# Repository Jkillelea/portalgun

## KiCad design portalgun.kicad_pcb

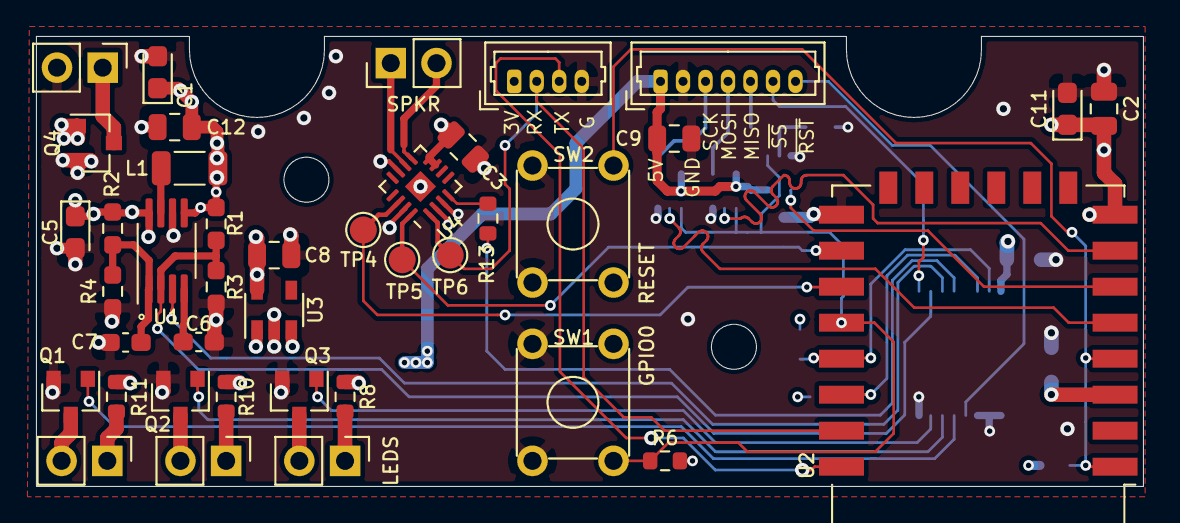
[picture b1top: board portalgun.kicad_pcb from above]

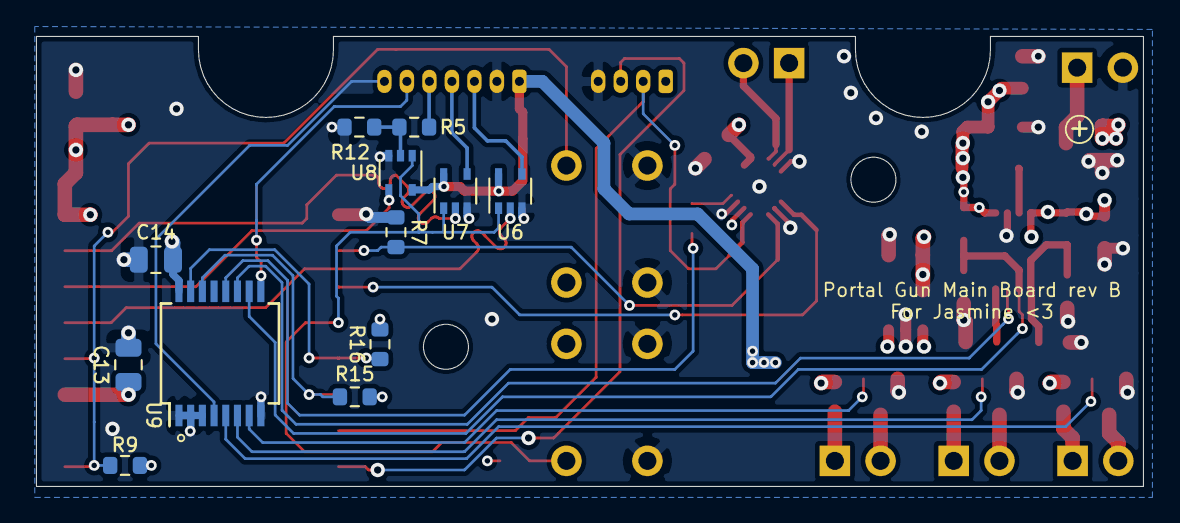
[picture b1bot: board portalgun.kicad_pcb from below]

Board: 4 copper layers, 61.5 x 25.0 mm, 54 parts (12 on the bottom side), 40 nets.

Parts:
C1, C5, C11: 10uF; CP_EIA-2012-15_AVX-P
C2, C3, C8, C9, C12, C13, C14: 1uF; C_0805_2012Metric
C6: 200nF; C_0603_1608Metric_Pad1.08x0.95mm_HandSolder
C7: 10pF; C_0603_1608Metric_Pad1.08x0.95mm_HandSolder
H1, H2: MountingHole; MountingHole_2.5mm
J1, J3, J4, J5, J10: Conn_01x02_Male; PinHeader_1x02_P2.54mm_Vertical
J2: Conn_01x07_Male; Molex_PicoBlade_53047-0710_1x07_P1.25mm_Vertical
J9: Conn_01x04_Female; Molex_PicoBlade_53047-0410_1x04_P1.25mm_Vertical
L1: 10uH; L_1206_3216Metric
Q1, Q2, Q3: BS316N; SOT-23
Q4: Q_PMOS_DGS; SOT-23
R1: 56k; R_0603_1608Metric_Pad0.98x0.95mm_HandSolder
R2: 383k; R_0603_1608Metric_Pad0.98x0.95mm_HandSolder
R3: 47k; R_0603_1608Metric_Pad0.98x0.95mm_HandSolder
R4: 120k; R_0603_1608Metric_Pad0.98x0.95mm_HandSolder
R5: 1k; R_0603_1608Metric
R6, R7, R9, R12, R15, R16: 10k; R_0603_1608Metric
R8, R10, R11: 200; R_0603_1608Metric
R13: 634kR; R_0603_1608Metric
SW1, SW2: SW_MEC_5E; SW_TH_Tactile_Omron_B3F-10xx
TP4: I2S_LRCIN_TP; TestPoint_Pad_D1.5mm
TP5: I2S_BCLK_TP; TestPoint_Pad_D1.5mm
TP6: I2S_DIN_TP; TestPoint_Pad_D1.5mm
U1: NCP1421; MSOP-8_3x3mm_P0.65mm
U2: ESP-12F; ESP-12E
U3: MIC5504-3.3YM5; SOT-23-5
U4: MAX98357AETE; TQFN-16-1EP_3x3mm_P0.5mm_EP1.23x1.23mm
U6, U7, U8: 74AHC1G125; SOT-353_SC-70-5
U9: PCA9534; SSOP-16_5.3x6.2mm_P0.65mm

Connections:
+3V3: C2.1, C3.1, C8.1, C11.1, C13.1, C14.1, J9.1, R6.2, R9.1, R15.1, R16.2, U2.3, U2.8, U3.5, U4.2, U4.7, U4.8, U9.16
+5V: C5.1, C9.1, J2.1, R2.1, R8.2, R10.2, R11.2, U1.8, U3.1, U3.3, U6.5, U7.5, U8.5
/Audio DAC/AOUT+: J4.1, U4.10
/Audio DAC/AOUT-: J4.2, U4.9
/Audio DAC/~SD_MODE: R13.1, U4.4
/Audio DAC/~SHUTDOWN: R13.2, U9.12
/EXT_MISO: J2.5, R5.1
/EXT_MOSI: J2.4, U7.4
/EXT_SCK: J2.3, U6.4
/bat+: J1.1, Q4.3
/ncp_fb: C7.1, R2.2, R4.1, U1.1
/ncp_lx: L1.2, U1.7
/ncp_ref: C6.1, U1.4
/~rst: R9.2, SW2.4, U2.1, U2.4
ESP_RXD: J9.2, TP6.1, U2.21, U4.1
ESP_TXD: J9.3, U2.22
GND: C1.2, C2.2, C3.2, C5.2, C6.2, C7.2, C8.2, C9.2, C11.2, C12.2, C13.2, C14.2, J1.2, J2.2, J9.4, Q1.2, Q2.2, Q3.2, Q4.2, R3.2, R4.2, R7.1, R12.1, SW1.1, SW1.2, SW2.1, SW2.2, U1.6, U2.15, U3.2, U4.3, U4.11, U4.15, U4.17, U6.3, U7.3, U8.3, U9.1, U9.2, U9.3, U9.8
I2S_BCLK: R7.2, TP5.1, U2.16, U4.16
I2S_LRCLK: TP4.1, U2.17, U4.14
LED1: Q1.1, U9.5
LED2: Q2.1, U9.6
LED3: Q3.1, U9.7
NCP_LBI_EN: R1.2, R3.1, U1.2, U9.10
NCP_LBO: U1.3, U9.11
unnamed: J3.1, R8.1
unnamed: J3.2, Q3.3
unnamed: J5.1, R10.1
unnamed: J5.2, Q2.3
unnamed: J10.1, R11.1
unnamed: J10.2, Q1.3
unnamed: R5.2, R12.2, U8.2
SCL: R15.2, U2.20, U9.14
SDA: R16.1, U2.19, U9.15
SPI1_MISO: U2.6, U8.4
SPI1_MOSI: U2.7, U7.2
SPI1_SCK: U2.5, U6.2
VBAT: C1.1, C12.1, L1.1, Q4.1, R1.1, U1.5
~BUFFER_EN: R6.1, SW1.3, U2.18, U6.1, U7.1, U8.1
~DISPLAY_RST: J2.7, U9.4
~SPI1_SS: J2.6, U9.9

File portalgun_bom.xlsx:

Refs | Val | Footprint | Qty | Stock
> J1, J3-J5, J10 | Conn_01x02_Male | Connector_PinHeader_2.00mm:PinHeader_1x02_P2.00mm_Vertical | 5 | 5
J2 | Conn_01x07_Male | Connector_Molex:Molex_PicoBlade_53047-0710_1x07_P1.25mm_Vertical | 1 | 10
J9 | Conn_01x04_Female | Connector_Molex:Molex_PicoBlade_53047-0410_1x04_P1.25mm_Vertical | 1 | 10
> Q1-Q3 | BS316N | Package_TO_SOT_SMD:SOT-23 | 3 | 100
R1 | 56k | Resistor_SMD:R_0603_1608Metric_Pad0.98x0.95mm_HandSolder | 1 | 100
R2 | 383k | Resistor_SMD:R_0603_1608Metric_Pad0.98x0.95mm_HandSolder | 1 | 100
R3 | 47k | Resistor_SMD:R_0603_1608Metric_Pad0.98x0.95mm_HandSolder | 1 | 100
R4 | 120k | Resistor_SMD:R_0603_1608Metric_Pad0.98x0.95mm_HandSolder | 1 | 100
R5 | 1k | Resistor_SMD:R_0603_1608Metric | 1 | 100
> R8, R10, R11 | 200 | Resistor_SMD:R_0603_1608Metric | 3 | 100
> R6, R9, R15, R16 | 10k | Resistor_SMD:R_0603_1608Metric | 4 | 100
> SW1, SW2 | SW_MEC_5E | Button_Switch_THT:SW_TH_Tactile_Omron_B3F-10xx | 2 | 25
U3 | MIC5504-3.3YM5 | Package_TO_SOT_SMD:SOT-23-5 | 1 | 25
U5 | MIC5504-1.8YM5 | Package_TO_SOT_SMD:SOT-23-5 | 1 | 10
> U6-U8 | 74AHC1G125 | Package_TO_SOT_SMD:SOT-353_SC-70-5 | 3 | 25
U1 | NCP1421 | Package_SO:MSOP-8_3x3mm_P0.65mm | 1 | 4
> H1, H2 | MountingHole | MountingHole:MountingHole_2.5mm | 2 | 2
U4 | SGTL5000XNLA3 | Package_DFN_QFN:QFN-20-1EP_3x3mm_P0.4mm_EP1.65x1.65mm | 1 | 3
L1 | 10uH | Inductor_SMD:L_1206_3216Metric | 1 | 5
U2 | ESP-12F | RF_Module:ESP-12E | 1 | 5
> C1, C5, C11 | 10uF | Capacitor_Tantalum_SMD:CP_EIA-2012-15_AVX-P | 3 | 8
C4 | 100nF | Capacitor_SMD:C_0603_1608Metric | 1 | 10
C6 | 200nF | Capacitor_SMD:C_0603_1608Metric_Pad1.08x0.95mm_HandSolder | 1 | 10
C7 | 10pF | Capacitor_SMD:C_0603_1608Metric_Pad1.08x0.95mm_HandSolder | 1 | 10
> C3, C8-C10 | 1uF | Capacitor_SMD:C_0603_1608Metric | 4 | 10
C2 | 10uF | Capacitor_SMD:C_0805_2012Metric | 1 | 80

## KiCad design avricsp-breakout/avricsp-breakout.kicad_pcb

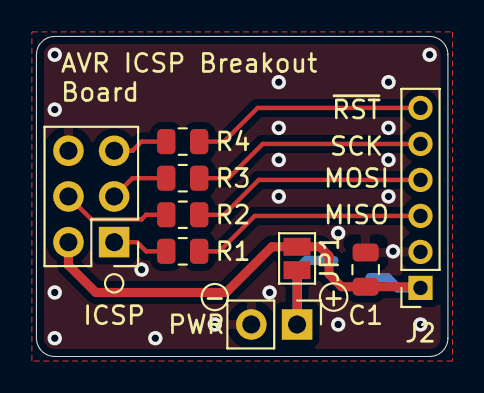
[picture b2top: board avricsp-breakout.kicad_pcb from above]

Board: 2 copper layers, 22.9 x 17.8 mm, 10 parts (1 on the bottom side), 11 nets.

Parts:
C1: 1uf; C_0805_2012Metric
ICSP: AVR-ISP-6; PinHeader_2x03_P2.54mm_Vertical
J2: Conn_01x06; PinSocket_1x06_P2.00mm_Vertical
JP1: SolderJumper_2_Open; SolderJumper-2_P1.3mm_Open_Pad1.0x1.5mm
PWR: Conn_01x02; PinHeader_1x02_P2.54mm_Vertical
Q1: Si2333CDS; SOT-23
R1, R2, R3, R4: 1k; R_0805_2012Metric

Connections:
/MISO: J2.3, R1.1
/MOSI: J2.4, R2.1
/SCK: J2.5, R3.1
/Vraw+: JP1.2, PWR.1, Q1.3
/~RST: J2.6, R4.1
GND: C1.2, ICSP.6, J2.2, PWR.2, Q1.1
unnamed: ICSP.1, R1.2
unnamed: ICSP.3, R3.2
unnamed: ICSP.4, R2.2
unnamed: ICSP.5, R4.2
VCC: C1.1, ICSP.2, J2.1, JP1.1, Q1.2

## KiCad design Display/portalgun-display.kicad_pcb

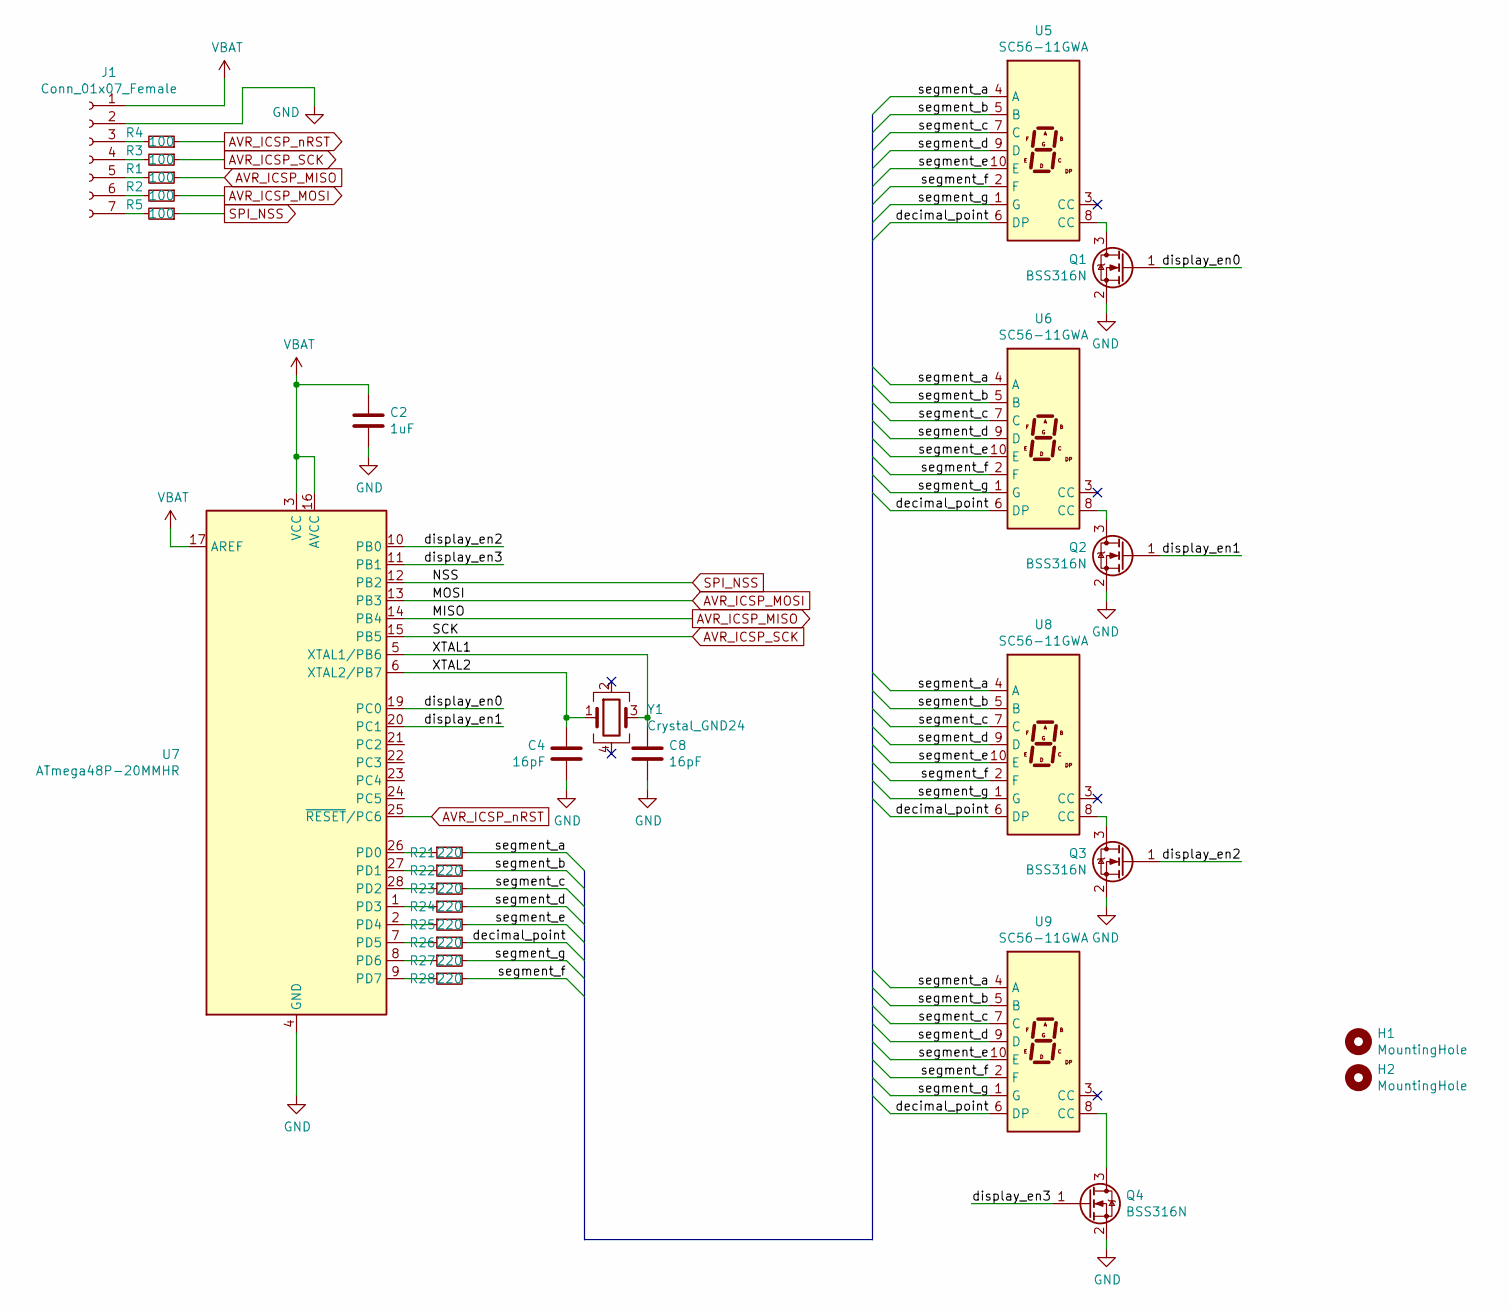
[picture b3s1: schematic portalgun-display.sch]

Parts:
C2: 1uF; C_0603_1608Metric
C4, C8: 16pF; C_0603_1608Metric
H1, H2: MountingHole; MountingHole_2.7mm
J1: Conn_01x07_Female; Molex_PicoBlade_53047-0710_1x07_P1.25mm_Vertical
Q1, Q2, Q3, Q4: BSS316N; SOT-23
R1, R2, R3, R4, R5: 100; R_0603_1608Metric_Pad0.98x0.95mm_HandSolder
R21, R22, R23, R24, R25, R26, R27, R28: 220; R_0603_1608Metric
U5, U6, U8, U9: SC56-11GWA
U7: ATmega48P-20MMHR; QFN-28-1EP_4x4mm_P0.45mm_EP2.4x2.4mm
Y1: Crystal_GND24; Crystal_SMD_3225-4Pin_3.2x2.5mm

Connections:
/XTAL1: C8.1, U7.5 (XTAL1/PB6), Y1.3
/XTAL2: C4.1, U7.6 (XTAL2/PB7), Y1.1
/decimal_point: R26.2, U5.6 (DP), U6.6 (DP), U8.6 (DP), U9.6 (DP)
/display_en0: Q1.1 (G), U7.19 (PC0)
/display_en1: Q2.1 (G), U7.20 (PC1)
/display_en2: Q3.1 (G), U7.10 (PB0)
/display_en3: Q4.1 (G), U7.11 (PB1)
/segment_a: R21.2, U5.4 (A), U6.4 (A), U8.4 (A), U9.4 (A)
/segment_b: R22.2, U5.5 (B), U6.5 (B), U8.5 (B), U9.5 (B)
/segment_c: R23.2, U5.7 (C), U6.7 (C), U8.7 (C), U9.7 (C)
/segment_d: R24.2, U5.9 (D), U6.9 (D), U8.9 (D), U9.9 (D)
/segment_e: R25.2, U5.10 (E), U6.10 (E), U8.10 (E), U9.10 (E)
/segment_f: R28.2, U5.2 (F), U6.2 (F), U8.2 (F), U9.2 (F)
/segment_g: R27.2, U5.1 (G), U6.1 (G), U8.1 (G), U9.1 (G)
AVR_ICSP_MISO: R1.1, U7.14 (PB4)
AVR_ICSP_MOSI: R2.1, U7.13 (PB3)
AVR_ICSP_SCK: R3.1, U7.15 (PB5)
AVR_ICSP_nRST: R4.1, U7.25 (~RESET~/PC6)
GND: C2.2, C4.2, C8.2, J1.2, Q1.2 (S), Q2.2 (S), Q3.2 (S), Q4.2 (S), U7.4 (GND), U7.18 (GND), U7.29 (GND)
unnamed: J1.3, R4.2
unnamed: J1.4, R3.2
unnamed: J1.5, R1.2
unnamed: J1.6, R2.2
unnamed: J1.7, R5.2
unnamed: Q1.3 (D), U5.8 (CC)
unnamed: Q2.3 (D), U6.8 (CC)
unnamed: Q3.3 (D), U8.8 (CC)
unnamed: Q4.3 (D), U9.8 (CC)
unnamed: R21.1, U7.26 (PD0)
unnamed: R22.1, U7.27 (PD1)
unnamed: R23.1, U7.28 (PD2)
unnamed: R24.1, U7.1 (PD3)
unnamed: R25.1, U7.2 (PD4)
unnamed: R26.1, U7.7 (PD5)
unnamed: R27.1, U7.8 (PD6)
unnamed: R28.1, U7.9 (PD7)
SPI_NSS: R5.1, U7.12 (PB2)
VBAT: C2.1, J1.1, U7.3 (VCC), U7.16 (AVCC), U7.17 (AREF)

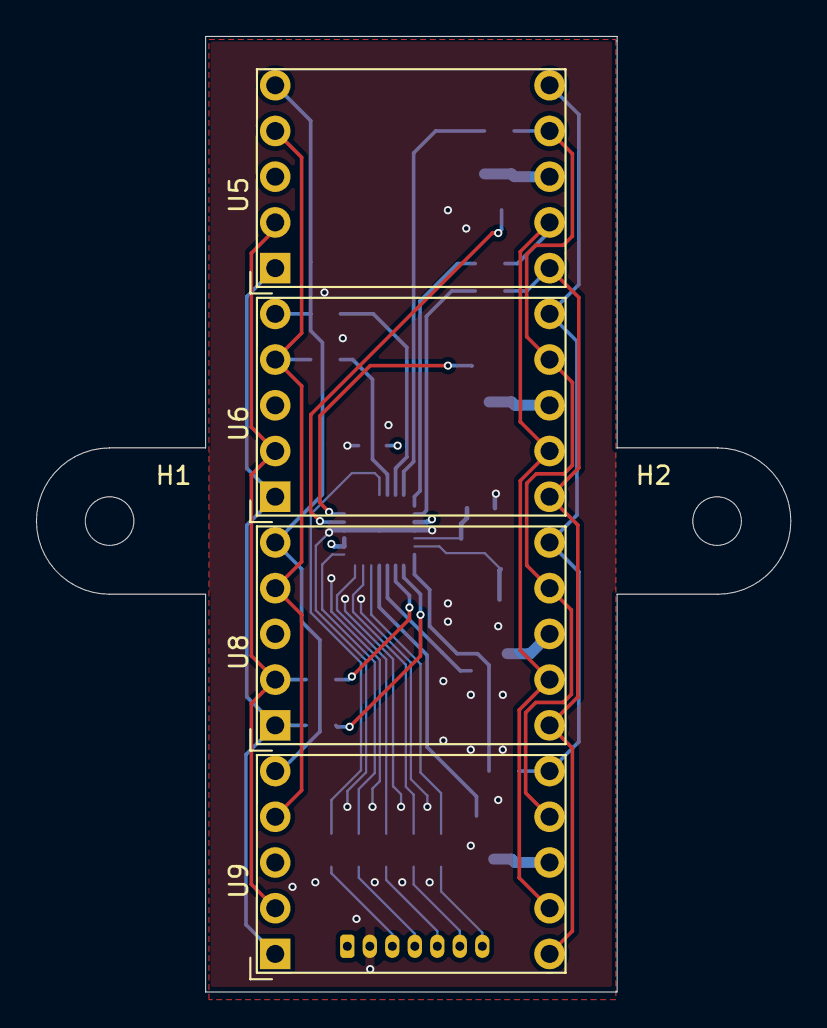
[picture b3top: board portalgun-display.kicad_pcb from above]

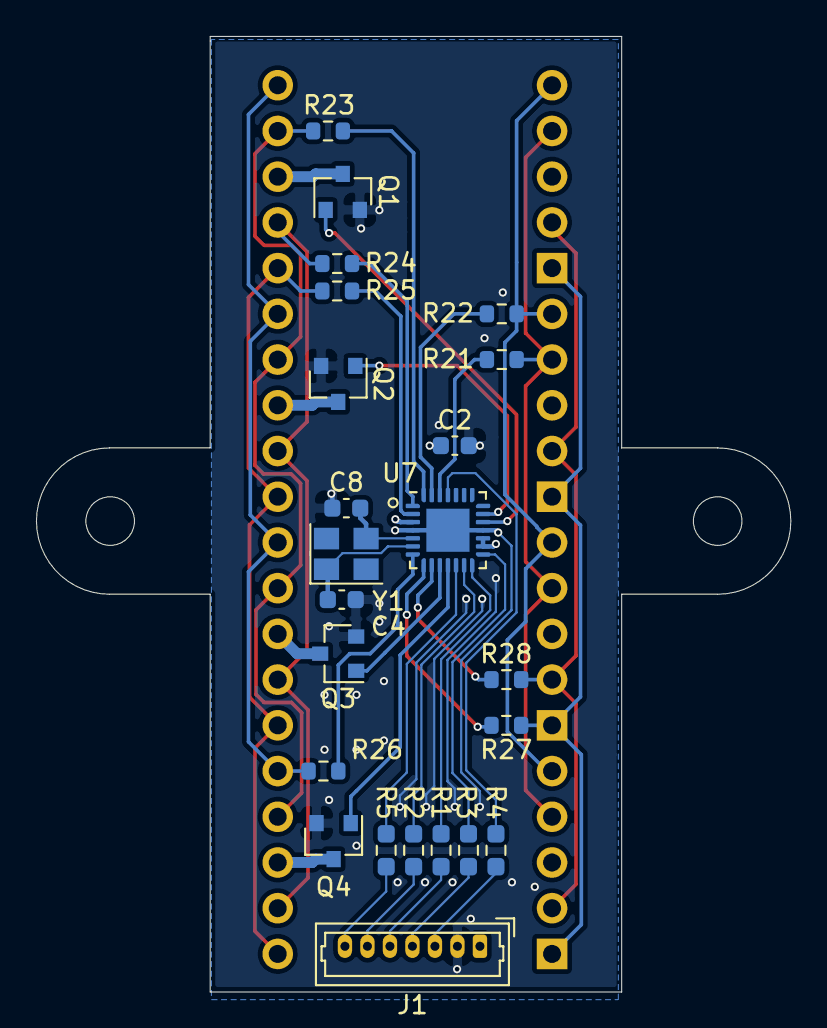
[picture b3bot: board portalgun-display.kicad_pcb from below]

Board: 4 copper layers, 41.9 x 53.1 mm, 29 parts (23 on the bottom side), 38 nets.

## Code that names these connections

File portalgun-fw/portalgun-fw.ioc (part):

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PA6.Mode=Full_Duplex_Master
PA7.Mode=Full_Duplex_Master
PA10.Mode=I2C
Mcu.UserName=STM32L011G4Ux
PA0-CK_IN.Mode=Asynchronous
PB6.GPIO_Label=LBO
RCC.SYSCLKSource=RCC_SYSCLKSOURCE_PLLCLK
PB5.GPIOParameters=GPIO_Label
PA13.Signal=SYS_SWDIO
PB4.GPIOParameters=GPIO_Label
PA9.Mode=I2C
PA9.Signal=I2C1_SCL
PB6.Signal=GPIO_Input
PA1.Signal=LPUART1_TX
PA5.Signal=SPI1_SCK
RCC.HSE_VALUE=8000000
board=custom
PA0-CK_IN.Signal=LPUART1_RX
PA1.Mode=Asynchronous
PB4.GPIO_Label=ENCODER_B
PB1.GPIO_Speed=GPIO_SPEED_FREQ_VERY_HIGH
PA14.Mode=Serial_Wire
PB1.GPIO_Label=LED_DATA
PB3.GPIOParameters=GPIO_Label
PA13.Mode=Serial_Wire
Mcu.Name=STM32L011G(3-4)Ux
PB6.GPIOParameters=GPIO_Label
PB1.PinState=GPIO_PIN_SET
PB3.Signal=GPIO_Input
RCC.SYSCLKFreq_VALUE=32000000
Mcu.Package=UFQFPN28
PB5.Signal=GPIO_Input
PB1.Signal=GPIO_Output
PA6.Signal=SPI1_MISO
PA10.Signal=I2C1_SDA
PA14.Signal=SYS_SWCLK
PB5.GPIO_Label=ENCODER_A
PB4.Signal=GPIO_Input
PB1.GPIOParameters=GPIO_Speed,PinState,GPIO_Label
PA7.Signal=SPI1_MOSI
PA5.Mode=Full_Duplex_Master
PB3.GPIO_Label=SWITCH

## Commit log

2021-02-06 Firmware
2021-02-06 Remove build artifacts
2021-02-07 My custom register definition header
2021-02-07 use custom register definitions
2021-02-07 improve make clean
2021-03-26 Main Board Rev A files
2021-03-26 Display controller files
2021-03-26 Display schematic
2021-03-29 Working on firmware now that display is built
2021-03-29 Misc code tweaks
2021-03-29 Tweaks
2021-03-30 Schematic
2021-03-31 Misc tweaks
2021-03-31 add rendering buffer
2021-04-25 Cleanup + comments
2021-04-25 Name changes + timing changes for interrupt
2021-06-27 Rev B Portal Gun Mainboard as ordered
2021-06-27 Rev B Output files
2021-06-27 New audio DAC symbol
2021-06-27 Misc AVR changes
2021-06-28 Formatting
2021-08-22 Updates. Firmware running on main board rev B
2021-08-23 Update display
